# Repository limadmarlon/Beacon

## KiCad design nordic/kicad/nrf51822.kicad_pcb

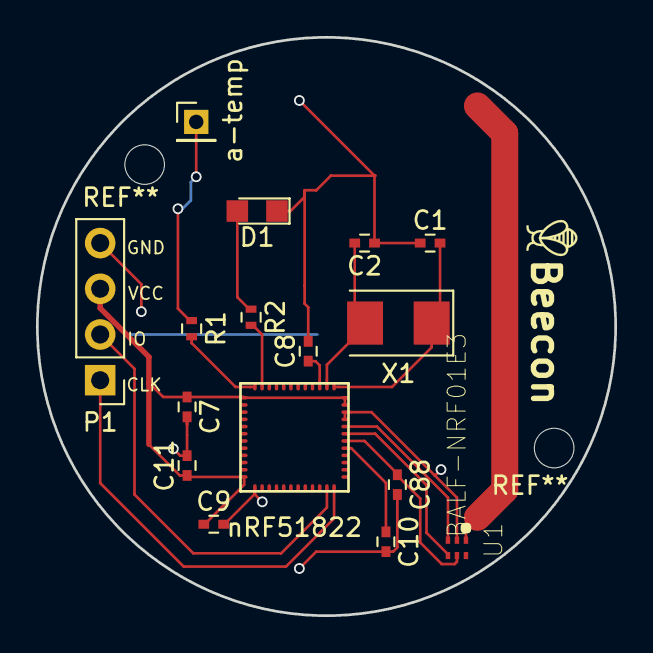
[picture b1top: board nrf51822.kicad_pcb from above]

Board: 2 copper layers, 32.1 x 32.1 mm, 18 parts (1 on the bottom side), 15 nets.

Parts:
A*: Antenna
BT1: Battery; cr2032_bat_holder
C1, C2, C7, C8, C9, C10, C11, C88: C_Small; C_0402
D1: LED; LED_0805
P1: CONN_01X04; Pin_Header_Straight_1x04_Pitch2.54mm
R1, R2: R_Small; R_0402
U1: BALF-NRF01E3; LGA6S60X50P2X3_100X150X48
X1: Crystal; Crystal_SMD_5032-2pin_5.0x3.2mm
a-temp: CONN_01X01; Pin_Header_Straight_1x01_Pitch2.00mm
nRF51822: nRF51822

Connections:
GND: BT1.2, C1.1, C2.1, C7.1, C8.2, C9.2, C10.2, C11.2, C88.2, D1.1, P1.4, U1.2, nRF51822.13, nRF51822.33, nRF51822.34
unnamed: C1.2, X1.1, nRF51822.37
unnamed: C2.2, X1.2, nRF51822.38
unnamed: C8.1, nRF51822.39
unnamed: C10.1, nRF51822.29
unnamed: C88.1, U1.5, nRF51822.30
unnamed: D1.2, R2.1
unnamed: P1.1, nRF51822.24
unnamed: P1.2, nRF51822.23
unnamed: R1.1, a-temp.1
unnamed: R1.2, nRF51822.48
unnamed: R2.2, nRF51822.47
unnamed: U1.3, nRF51822.32
unnamed: U1.4, nRF51822.31
VCC: BT1.1, C7.2, C9.1, C11.1, P1.3, nRF51822.1, nRF51822.12, nRF51822.35, nRF51822.36

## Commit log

2017-05-28 esquematico
2017-05-28 Added BALF antenna's footprint; added maching network's antenna circuit values
2017-05-28 Corrections in the antenna's matching network
2017-05-28 PCB completo
2017-06-02 Visual Changes and new Battery pad
2017-06-05 Adicionado Mounting Holes.
2017-06-09 Adicionado pino pra anti-tampering, botão de reset e logo
2017-06-13 Component values updated; bom added
2017-07-09 Adicionado logo e pino pra Anti-tamper
2017-07-09 Adicionado componentes 3D
2017-07-13 Adicionado componentes 3d no diretório, aumentado a logo e colocado led para teste POST no lugar do botão de reset
2017-07-21 antena drobradinha
2017-07-26 feat(pcb) New Antenna
2017-07-26 Consertado antena
